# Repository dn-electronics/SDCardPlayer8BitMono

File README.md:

SDCardPlayer8BitMono
====================
Introduction
============
The SDCardPlayer8BitMono is a Mono 8-bit WAV player based on the populat Simple SD Audio Player by Elm-Chan 

Features
========
1. ATTINY85 microcontroller
2. Next track switch
3. Sound control
4. Power ON/OFF
5. Atmel Studio 6 programming file

Licence
=======
<p>This work is licensed under a <a href="http://www.creativecommons.org/licenses/by-sa/3.0" target="_blank">Creative Commons Attribution-ShareAlike 3.0 Unported License</a> 

Schematic
=========

Programming File Fuse Settings - ATTINY85
=========================================
Blow fuses before flashing program code

1. SPIEN: tick
2. BODLEVEL: 2V7
3. SUT_CKSL: PLLCLK_1KCK_14CK_64MS
4. EXT:  FF
5. HIGH: DD
6. LOW:  E1

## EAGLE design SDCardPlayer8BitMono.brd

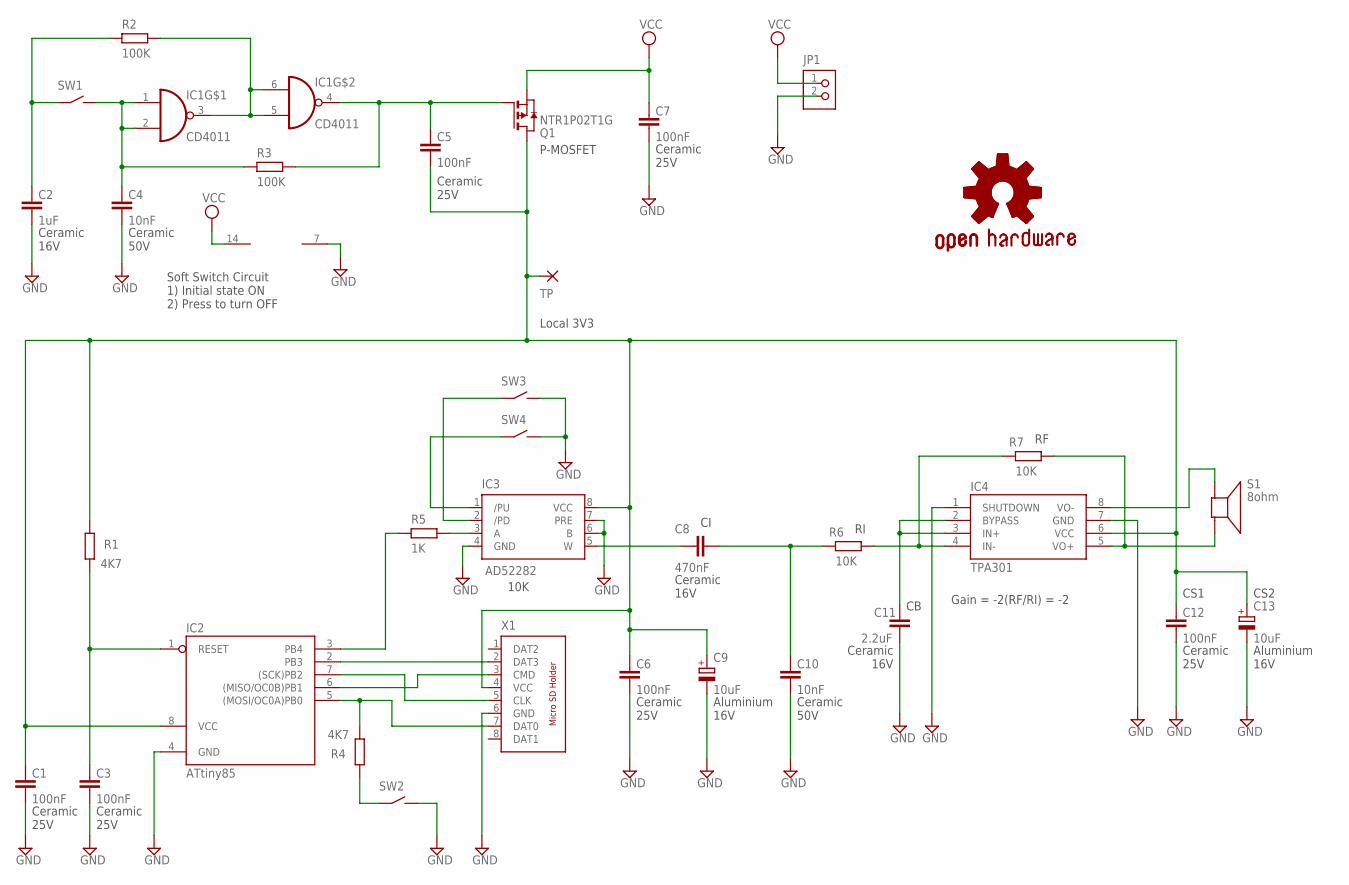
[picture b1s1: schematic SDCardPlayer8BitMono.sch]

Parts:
C1, C3, C5, C6, C7, C12: 100nF; P-0805
C2: 1uF; P-0805
C4, C10: 10nF; P-0805
C8: 470nF; P-0805
C9, C13: 10uF; P-CAPNICHICON-3MM
C11: 2.2uF; P-0805
GOLD_ORB_SM1: OSHWLOGO_GOLD_ORB_SM; OSHW2
IC1: CD4011; P-SOIC14
IC2: ATtiny85; P-DIL8
IC3: AD52282; P-SOT23-8E
IC4: TPA301; P-SO8
JP1: JST-XH-1X021; P-JST-XH-1X02
Q1: NTR1P02T1G; P-SOT23-3E
R1, R4: 4K7; P-0805
R2, R3: 100K; P-0805
R5: 1K; P-0805
R6, R7: 10K; P-0805
S1: 8ohm; P-JST-XH-1X02
SW1, SW2, SW3, SW4: SWITCH-2PIN4; P-JST-XH-1X02
TP: PAD; P-PAD127X127
X1: MICRO-SD-CARD-HOLDER; P-MICRO-SD-CARD-HOLDER

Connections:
GND: C1.2, C2.2, C3.2, C4.2, C6.2, C7.2, C9.2 (-), C10.2, C11.2, C12.2, C13.2 (-), IC1.7 (GND), IC2.4 (GND), IC3.4 (GND), IC3.6 (B), IC3.7 (PRE), IC4.1 (SHUTDOWN), IC4.7 (GND), JP1.2, SW2.2, SW3.2, SW4.2, X1.6 (GND)
unnamed: C3.1, IC2.1 (RESET), R1.1
unnamed: R4.2, SW2.1
unnamed: IC2.5 ((MOSI/OC0A)PB0), R4.1, X1.7 (DAT0)
unnamed: IC2.2 (PB3), X1.2 (DAT3)
unnamed: IC2.3 (PB4), R5.1
unnamed: IC1.3 (O), IC1.5 (I1), IC1.6 (I0), R2.2
unnamed: C4.1, IC1.1 (I0), IC1.2 (I1), R3.1, SW1.2
unnamed: C5.1, IC1.4 (O), Q1.1 (G), R3.2
unnamed: C8.2, C10.1, R6.1
unnamed: IC4.4 (IN-), R6.2, R7.1
unnamed: C2.1, R2.1, SW1.1
unnamed: C11.1, IC4.2 (BYPASS), IC4.3 (IN+)
unnamed: IC4.5 (VO+), R7.2, S1.2
unnamed: IC4.8 (VO-), S1.1
unnamed: C8.1, IC3.5 (W)
unnamed: IC3.2 (/PD), SW3.1
unnamed: IC3.1 (/PU), SW4.1
unnamed: IC3.3 (A), R5.2
unnamed: IC2.6 ((MISO/OC0B)PB1), X1.3 (CMD)
unnamed: C1.1, C5.2, C6.1, C9.1 (+), C12.1, C13.1 (+), IC2.8 (VCC), IC3.8 (VCC), IC4.6 (VCC), Q1.3 (D), R1.2, TP.P$1, X1.4 (VCC)
unnamed: IC2.7 ((SCK)PB2), X1.5 (CLK)
VCC: C7.1, IC1.14 (VCC), JP1.1, Q1.2 (S)

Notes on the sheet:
10K
Gain = -2(RF/RI) = -2
Ceramic 25V
Aluminium 16V
Ceramic 16V
CS1
CS2
Ceramic 50V
Soft Switch Circuit 1) Initial state ON 2) Press to turn OFF
P-MOSFET
Local 3V3

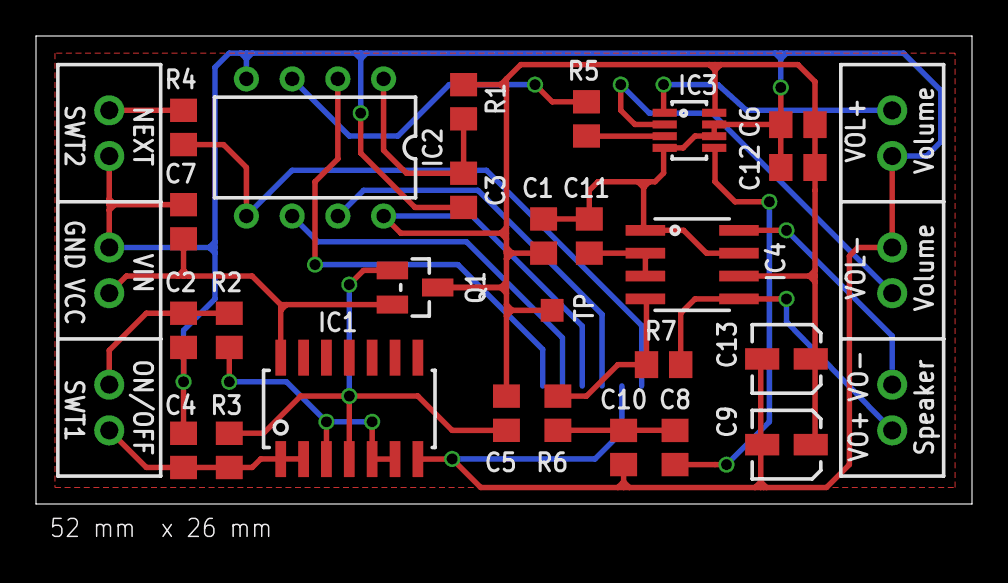
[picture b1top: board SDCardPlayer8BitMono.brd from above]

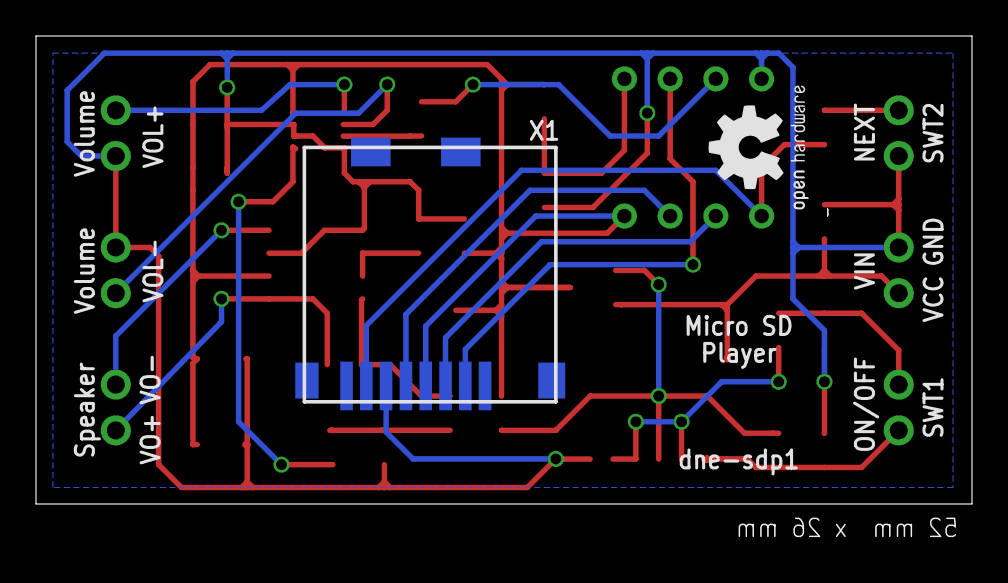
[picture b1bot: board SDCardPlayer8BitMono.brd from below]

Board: 2 copper layers, 52.0 x 28.4 mm, 34 parts (2 on the bottom side), 23 nets.

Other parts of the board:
E$1: OSHW2
